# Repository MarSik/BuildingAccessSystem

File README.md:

# NFC entry system using TI Tiva C platform - with DESfire support

The aim is to use the [Tiva C Launchpad](http://www.ti.com/tool/ek-tm4c123gxl) together with [PN532 NFC interface boards](https://www.adafruit.com/products/364) to create a secure building access system.

This project is based on [Elmu's code for Teensy](http://www.codeproject.com/Articles/1096861/DIY-electronic-RFID-Door-Lock-with-Battery-Backup).

## Development environment

Please download [Energia](http://energia.nu), use the `Tools / Board / Board manager` menu item to download the Tiva/Stellaris support files and open the `DoorOpenerSketch.ino` file in it.

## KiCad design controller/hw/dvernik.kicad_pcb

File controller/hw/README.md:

# Controller board

The PCB is not the best routed board ever, but I wanted a single copper layer board for a home made prototype to verify the functionality.

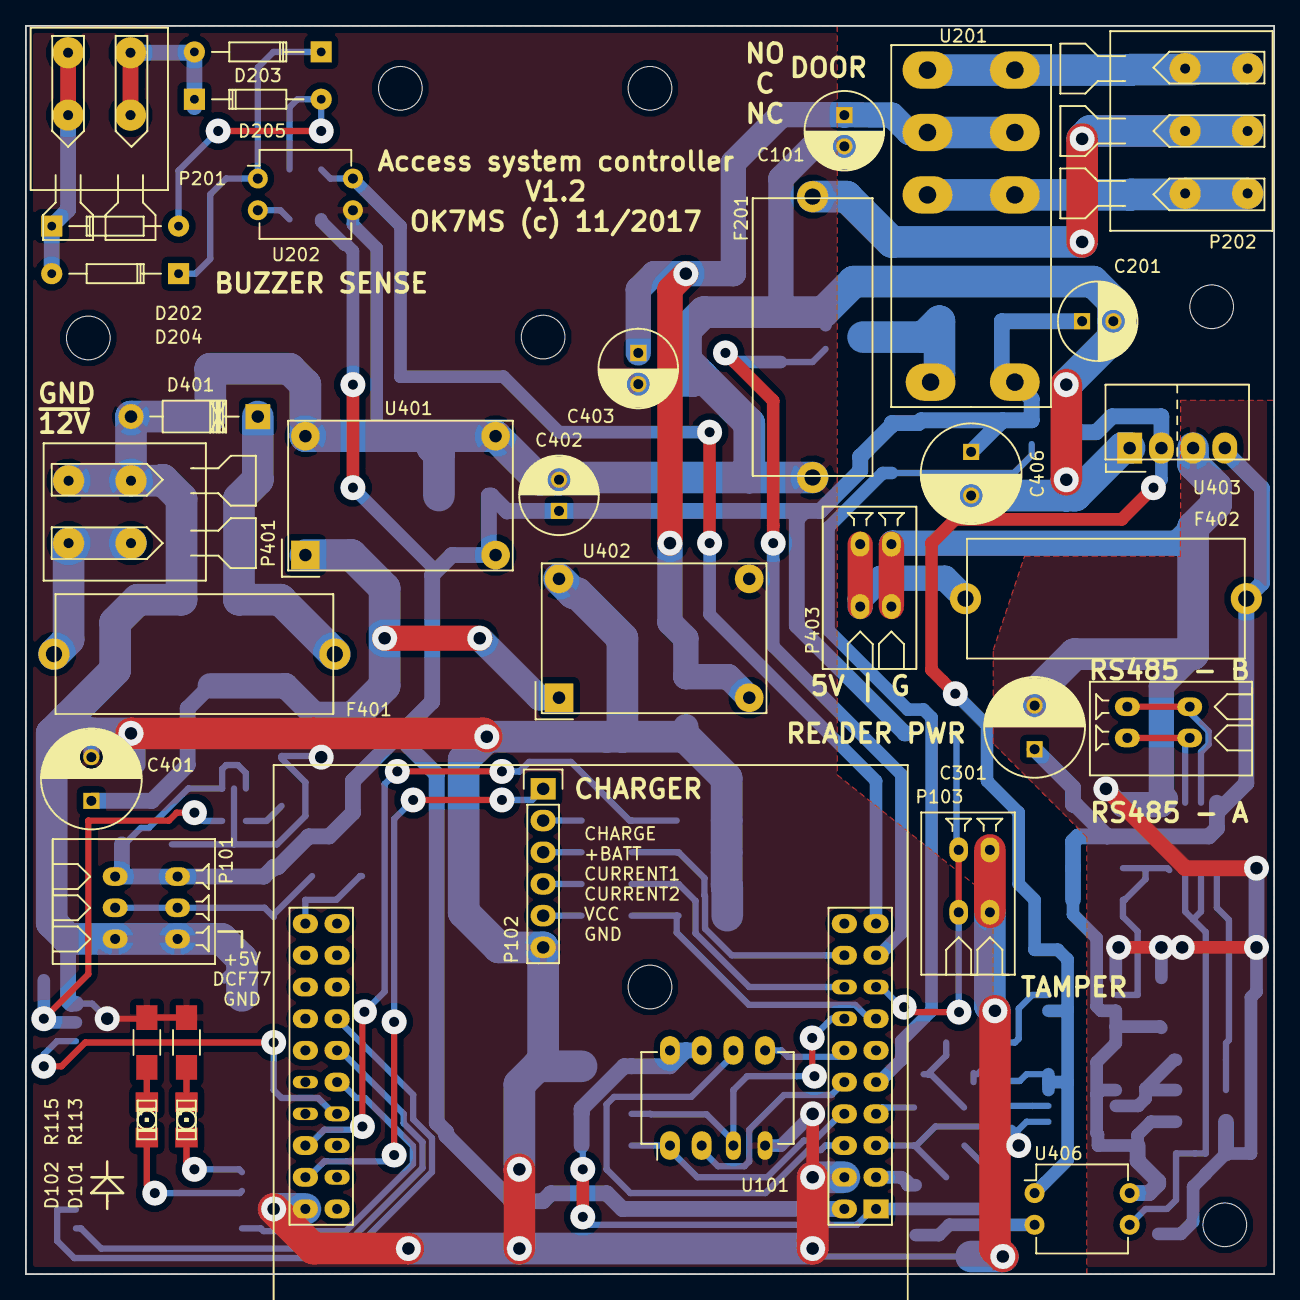
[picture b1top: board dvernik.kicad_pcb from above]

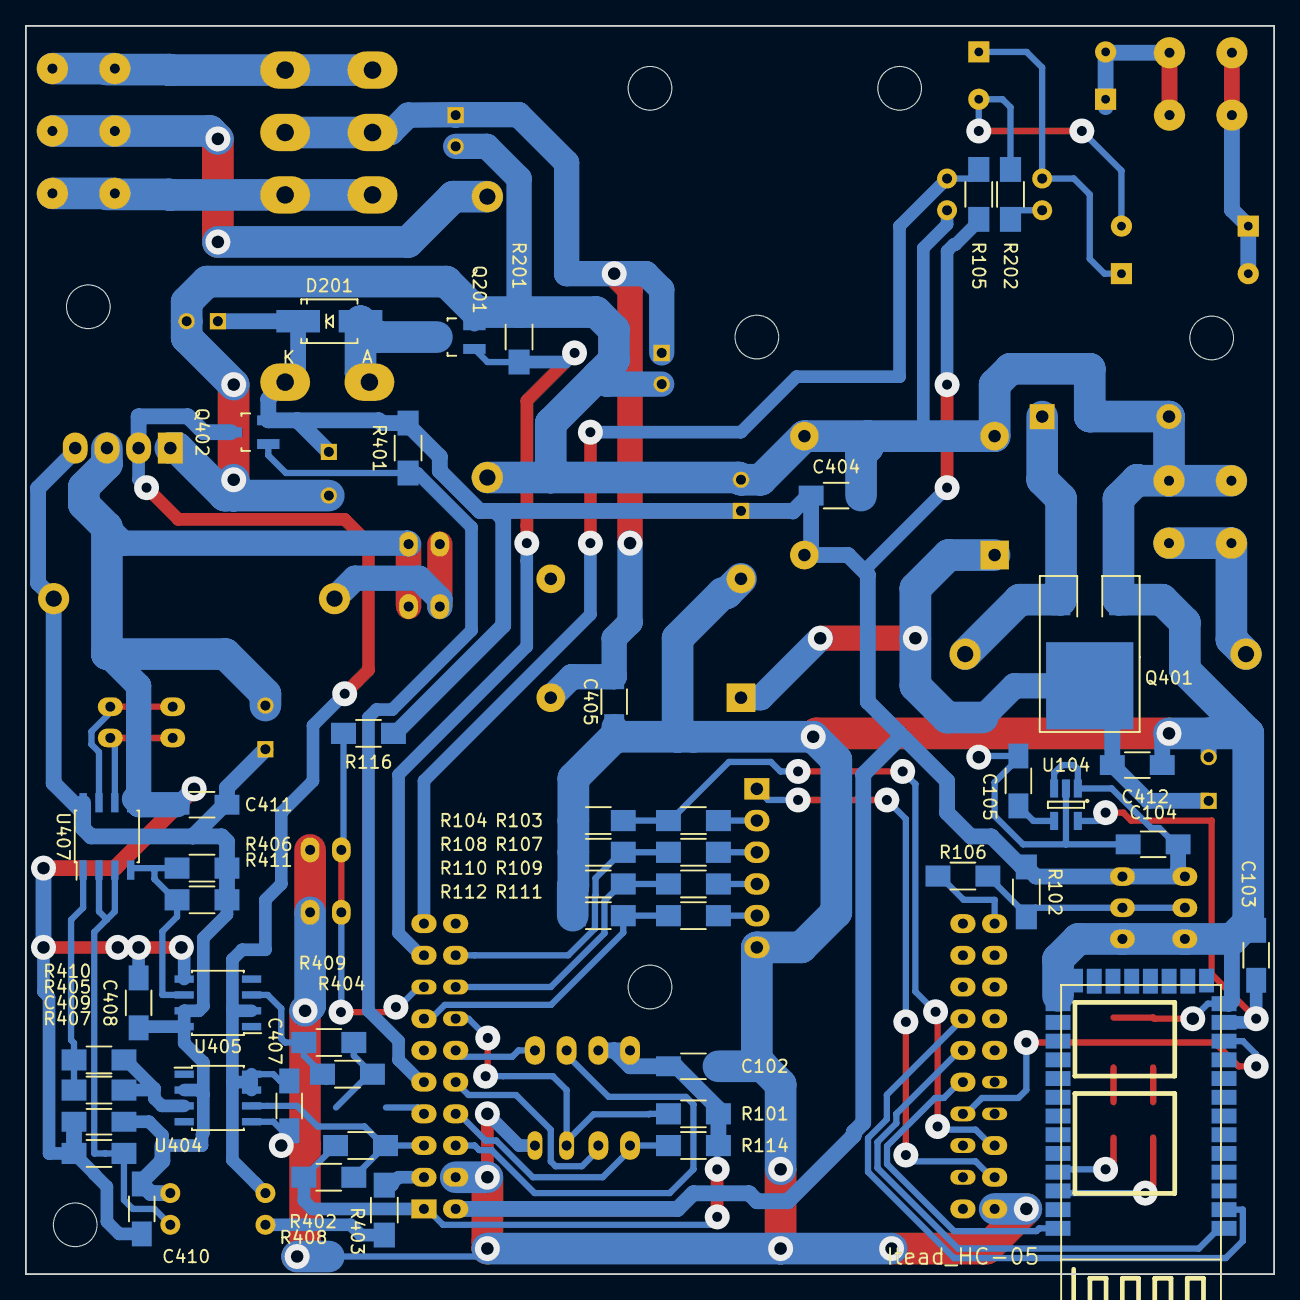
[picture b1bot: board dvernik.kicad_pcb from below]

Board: 2 copper layers, 100.0 x 100.0 mm, 83 parts (48 on the bottom side), 61 nets.

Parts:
C101, C201, C402, C403: Jamicon_220uF_16V_TKP; C_Radial_D6.3_L11.2_P2.5
C102, C104, C105, C404, C405, C412: C; C_1206_HandSoldering
C103, C407, C408, C409, C410, C411: 100n; C_1206_HandSoldering
C301, C401, C406: Jamicon_220uF_25V; C_Radial_D8_L11.5_P3.5
D101, D102: LED; LED-1206
D201: SK110; Diode-SMA_Handsoldering
D202, D203, D204, D205: SD103A; Diode_DO-35_SOD27_Horizontal_RM10
D401: BZX85C15; Diode_DO-41_SOD81_Horizontal_RM10
F201, F401, F402: FUSE; Fuse_5x20_Schurter-0031-8201
P101: WAGO233; Wire-3_Wago-233-P2.5mm
P102: CONN_01X06; Pin_Header_Straight_1x06
P103: CONN_01X02; Wire-2_Wago-233-P2.5mm
P201, P401: WAGO255; Wire-2_WAGO-255_P5mm_HandSoldering
P202: WAGO255; Wire-3_WAGO-255_P5mm_HandSoldering
P402, P403: Wago_233-502; Wire-2_Wago-233-P2.5mm
Q201: 2N7002K; SOT-23_HandSoldering
Q401: IRFU9024; DPAK_HandSoldering
Q402: IRLML6402; SOT-23_HandSoldering
R101, R102, R105, R114, R401, R407: 10k; R_1206_HandSoldering
R103, R107, R109, R111: 100k; R_1206_HandSoldering
R104, R108, R110, R112: 25k; R_1206_HandSoldering
R106: 0; R_1206_HandSoldering
R113, R115, R116, R201, R202, R403: R; R_1206_HandSoldering
R402, R404, R405, R406, R408, R409, R410, R411: 1k; R_1206_HandSoldering
U101: A25L40P; DIP-8_W300mil_LongPads
U102: EK-TM4C123GXL; TI-Launchpad_4-Ports_LargePads
U103: Itead_HC-05; RF_HC-0X_Itead_HandSoldering
U104: LP2992AIM5-3.3CT-ND; SOT-23-5_HandSoldering
U201: JQX-14FC22CS8-5.0; Relay_JQX-14FC_L5_HandSoldering
U202, U406: Cosmo_1010-817; DIP-4_W300mil
U401, U402: Mini-360; DcDc_MH_MINI_360
U403: ROE-0505S; DcDc_Roe_SIP-4
U404, U405: HCPL-0601-500E; SOIC-8_3.9x4.9mm_Pitch1.27mm
U407: SN75176BDR; SOIC-8_3.9x4.9mm_Pitch1.27mm

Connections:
+3V3: C102.1, R101.1, R114.1, R402.2, R408.2, U101.7, U101.8, U102.1.01
+5V: C104.1, C201.1, C402.1, C404.1, C406.1, D201.1, P101.1, Q402.2, R102.1, R105.1, R116.1, R401.2, U102.3.01, U104.1, U104.3, U201.8, U401.2
+5VA: C301.1, C408.1, C409.2, C410.2, C411.2, F402.2, R406.1, R411.1, U403.4, U404.2, U405.7, U405.8, U406.4, U407.8
+12V: C101.1, C403.1, C405.1, U201.3, U201.6, U402.2
+BATT: P102.2, R103.1
/BATT_SENSE: R103.2, R104.1, U102.2.03
/BT_AT_~COMM: U102.4.05, U103.34
/BUZZ1: R105.2, U102.1.10, U202.4
/CHARGE: P102.1, U102.2.02
/CHARGE_SENSE1: P102.4, R109.1
/CHARGE_SENSE2: P102.3, R107.1
/CPU_RX: R402.1, R408.1, U102.1.03, U404.6
/CPU_RX_BT: U102.4.06, U103.1
/CPU_TX_BT: U102.4.07, U103.2
/DCF77: R106.2, U102.2.10
/DOOR1: Q201.1, R201.1, U102.1.09
/Door1/BUZZER_COM: F201.1, P202.2
/Door1/BUZZER_IN1: D203.2, D205.1, P201.1
/Door1/BUZZER_IN2: D202.1, D204.2, P201.2
/Door1/BUZZER_NC: P202.1, U201.2, U201.7
/Door1/BUZZER_NO: P202.3, U201.4, U201.5
/Door1/RELAYGND: D201.2, Q201.3, U201.1
/MEM_CS: R114.2, U101.1, U102.3.04
/MEM_MISO: U101.2, U102.3.05
/MEM_MOSI: U101.5, U102.3.06
/MEM_SCK: U101.6, U102.3.03
/MEM_WP: R101.2, U101.3, U102.3.07
/Power/PFUSED: D401.1, F401.1, Q401.3
/Power/PIN: F401.2, P401.2
/ReaderIntf/485A: P402.1, U407.6
/ReaderIntf/485B: P402.2, U407.7
/ReaderIntf/CPU_TX5: R404.2, R409.2
/ReaderIntf/DCDCIN5V: C407.2, Q402.3, U403.2, U404.7, U404.8, U405.2, U406.1
/ReaderIntf/UNSAFE_RX: R405.1, R410.1, U407.1
/ReaderIntf/UNSAFE_TX: R406.2, R411.2, U405.6, U407.4
/ReaderIntf/~READER_ON: Q402.1, R401.1
/TAMPER: P103.1, R116.2, U102.1.08
/~BT_RESET: U102.4.04, U103.11
/~TX_EN: R403.2, U102.1.02
GND: C101.2, C102.2, C103.2, C104.2, C105.2, C201.2, C401.2, C402.2, C403.2, C404.2, C405.2, C406.2, C407.1, C412.2, D401.2, F201.2, P101.3, P102.6, P103.2, P401.1, Q201.2, Q401.1, R104.2, R108.2, R110.2, R112.2, R113.1, R115.1, R201.2, U101.4, U102.2.01, U102.3.02, U103.13, U103.21, U103.22, U104.2, U202.3, U401.3, U401.4, U402.3, U402.4, U403.1, U404.5
GNDA: C301.2, C408.2, C409.1, C410.1, C411.1, P403.2, R407.2, U403.3, U405.5, U407.5
unnamed: C103.1, U103.12, U104.5
unnamed: C105.1, U104.4
unnamed: C401.1, C412.1, Q401.4, U401.1, U402.1
unnamed: D101.1, R113.2
unnamed: D101.2, U103.31
unnamed: D102.1, R115.2
unnamed: D102.2, U103.32
unnamed: D202.2, D205.2, R202.2
unnamed: D203.1, D204.1, U202.1
unnamed: F402.1, P403.1
unnamed: P101.2, R102.2, R106.1
unnamed: R107.2, R108.1, U102.3.09
unnamed: R109.2, R110.1, U102.3.08
unnamed: R111.2, R112.1, U102.1.07
unnamed: R202.1, U202.2
unnamed: R403.1, U406.2
unnamed: R404.1, R409.1, U405.3
unnamed: R405.2, R410.2, U404.3
unnamed: R407.1, U406.3, U407.2, U407.3
VCC: P102.5, R111.1

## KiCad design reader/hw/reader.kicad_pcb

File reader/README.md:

# remote RFID card reader with RS485 interface

## Building

- Install embedded cmake tooling (github.com/MarSik/embc)
- run `embc init mke04` to initialize the build environment
- run `embc build` to build

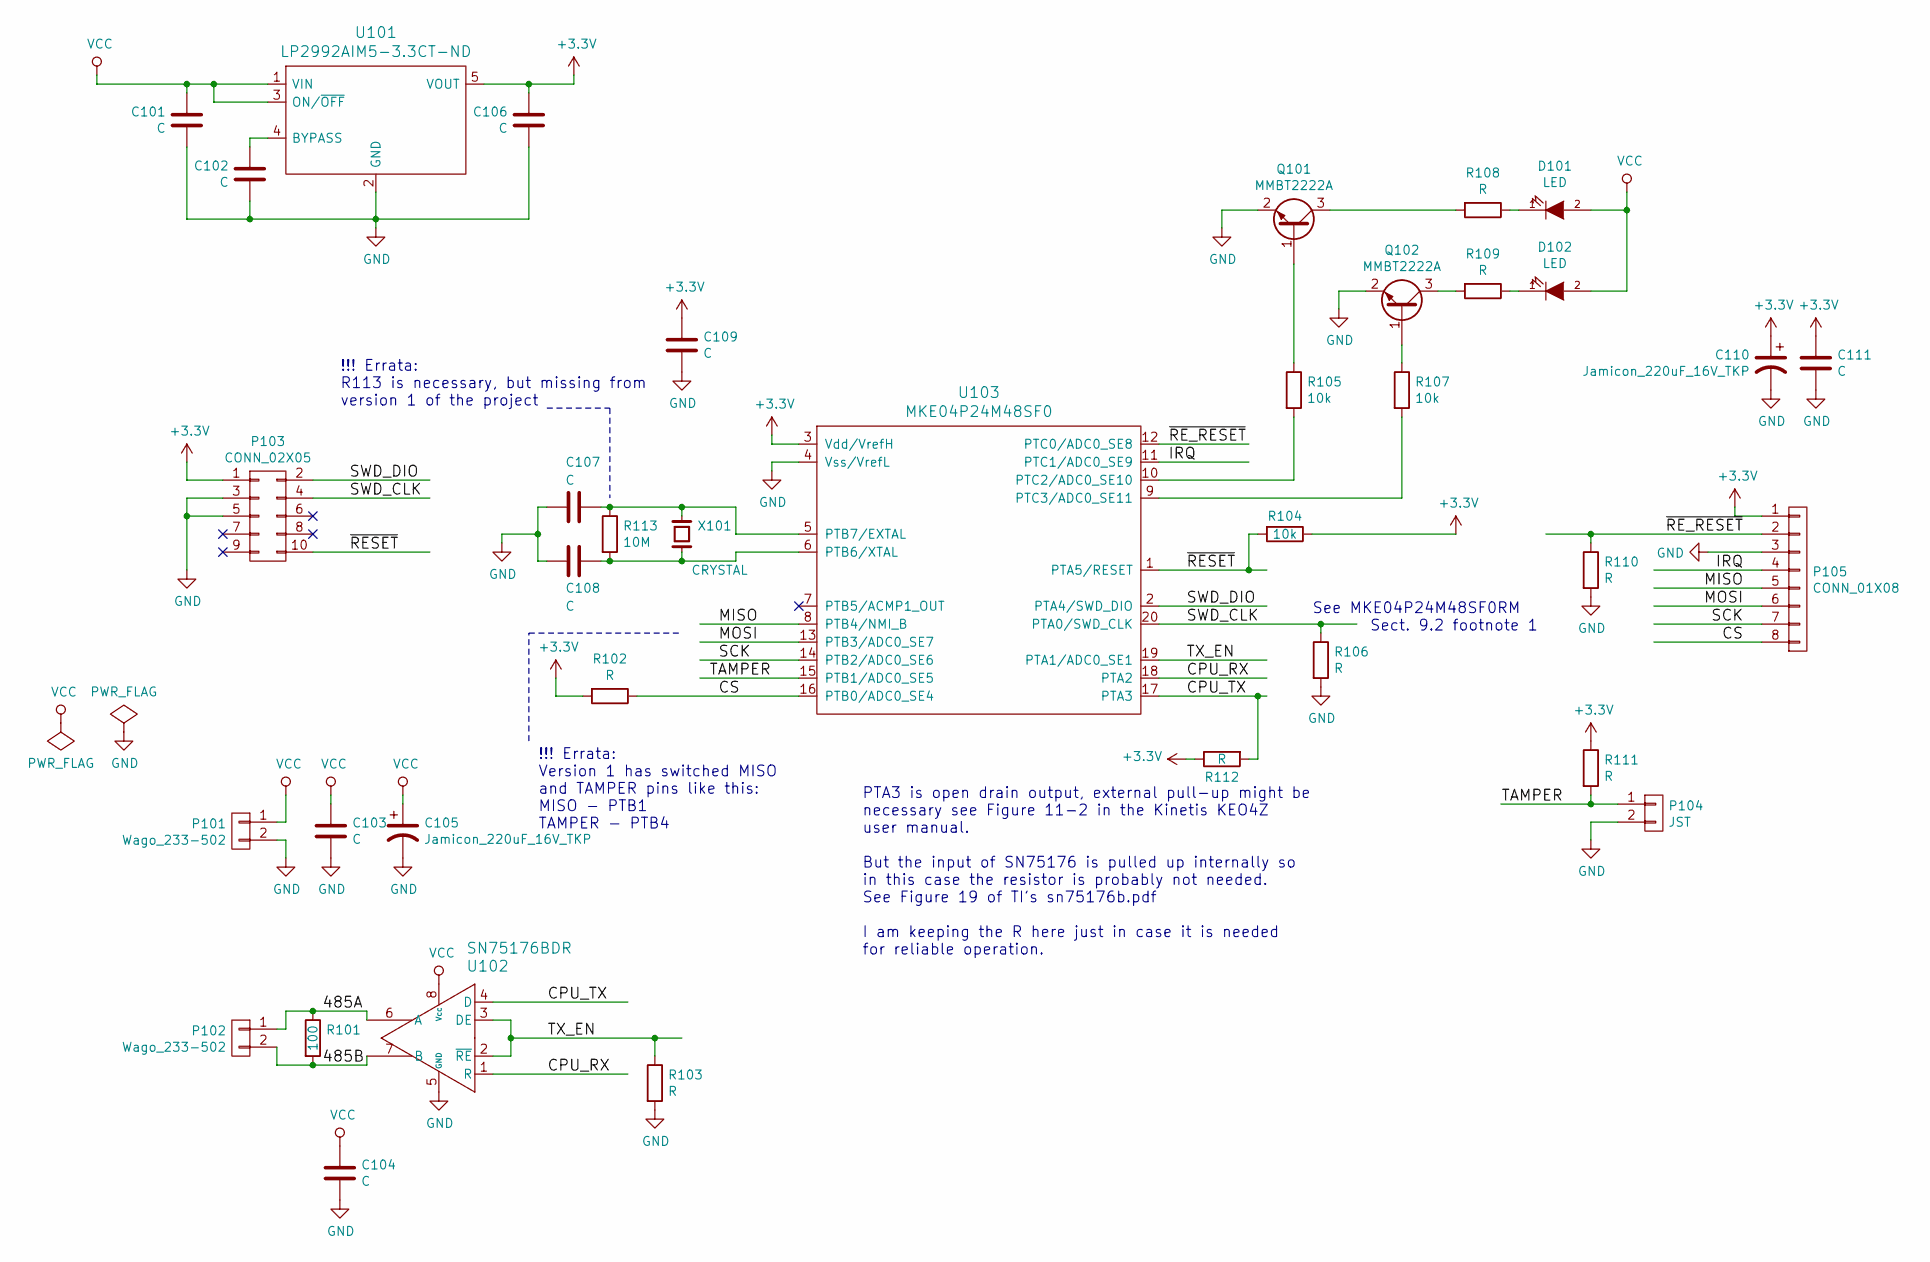
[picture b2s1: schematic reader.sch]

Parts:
C101, C102, C103, C104, C106, C107, C108, C109, C111: C; C_1206_HandSoldering
C105, C110: Jamicon_220uF_16V_TKP; C_Radial_D6.3_L11.2_P2.5
D101, D102: LED; LED-1206
P101, P102: Wago_233-502; Wire-2_Wago-233-P2.5mm
P103: CONN_02X05; Pin_Header_Straight_2x05
P104: JST; Connector_JST_PHR-2
P105: CONN_01X08; Pin_Header_Straight_1x08
Q101, Q102: MMBT2222A; SOT-23_HandSoldering
R101: 100; R_1206_HandSoldering
R102, R103, R106, R108, R109, R110, R111, R112: R; R_1206_HandSoldering
R104, R105, R107: 10k; R_1206_HandSoldering
R113: 10M; R_1206_HandSoldering
U101: LP2992AIM5-3.3CT-ND; SOT-23-5_HandSoldering
U102: SN75176BDR; SOIC-8_3.9x4.9mm_Pitch1.27mm
U103: MKE04P24M48SF0; SOIC-20_7.5x12.8mm_Pitch1.27mm
X101: CRYSTAL; Crystal_HC49-U_Vertical

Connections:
+3V3: C106.1, C109.1, C110.1, C111.1, P103.1, P105.1, R102.2, R104.1, R111.1, R112.1, U101.5 (VOUT), U103.3 (Vdd/VrefH)
/485A: P102.1, R101.1, U102.6 (A)
/485B: P102.2, R101.2, U102.7 (B)
/CPU_RX: U102.1 (R), U103.18 (PTA2)
/CPU_TX: R112.2, U102.4 (D), U103.17 (PTA3)
/CS: P105.8, R102.1, U103.16 (PTB0/ADC0_SE4)
/IRQ: P105.4, U103.11 (PTC1/ADC0_SE9)
/MISO: P105.5, U103.8 (PTB4/NMI_B)
/MOSI: P105.6, U103.13 (PTB3/ADC0_SE7)
/SCK: P105.7, U103.14 (PTB2/ADC0_SE6)
/SWD_CLK: P103.4, R106.1, U103.20 (PTA0/SWD_CLK)
/SWD_DIO: P103.2, U103.2 (PTA4/SWD_DIO)
/TAMPER: P104.1, R111.2, U103.15 (PTB1/ADC0_SE5)
/TX_EN: R103.1, U102.2 (~RE), U102.3 (DE), U103.19 (PTA1/ADC0_SE1)
/~RESET: P103.10, R104.2, U103.1 (PTA5/RESET)
/~RE_RESET: P105.2, R110.1, U103.12 (PTC0/ADC0_SE8)
GND: C101.2, C102.2, C103.2, C104.2, C105.2, C106.2, C107.2, C108.2, C109.2, C110.2, C111.2, P101.2, P103.3, P103.5, P104.2, P105.3, Q101.2 (E), Q102.2 (E), R103.2, R106.2, R110.2, U101.2 (GND), U102.5 (GND), U103.4 (Vss/VrefL)
unnamed: C102.1, U101.4 (BYPASS)
unnamed: C107.1, R113.1, U103.5 (PTB7/EXTAL), X101.1
unnamed: C108.1, R113.2, U103.6 (PTB6/XTAL), X101.2
unnamed: D101.1 (K), R108.1
unnamed: D102.1 (K), R109.1
unnamed: Q101.1 (B), R105.1
unnamed: Q101.3 (C), R108.2
unnamed: Q102.1 (B), R107.1
unnamed: Q102.3 (C), R109.2
unnamed: R105.2, U103.10 (PTC2/ADC0_SE10)
unnamed: R107.2, U103.9 (PTC3/ADC0_SE11)
VCC: C101.1, C103.1, C104.1, C105.1, D101.2 (A), D102.2 (A), P101.1, U101.1 (VIN), U101.3 (ON/~OFF), U102.8 (Vcc)

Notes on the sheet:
See MKE04P24M48SF0RM Sect. 9.2 footnote 1
PTA3 is open drain output, external pull-up might be necessary see Figure 11-2 in the Kinetis KEO4Z user manual. But the input of SN75176 is pulled up internally so in this case the resistor is probably not needed. See Figure 19 of TI's sn75176b.pdf I am keeping the R here just in case it is needed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
!!! Errata: Version 1 has switched MISO and TAMPER pins like this: MISO - PTB1 TAMPER - PTB4
!!! Errata: R113 is necessary, but missing from version 1 of the project

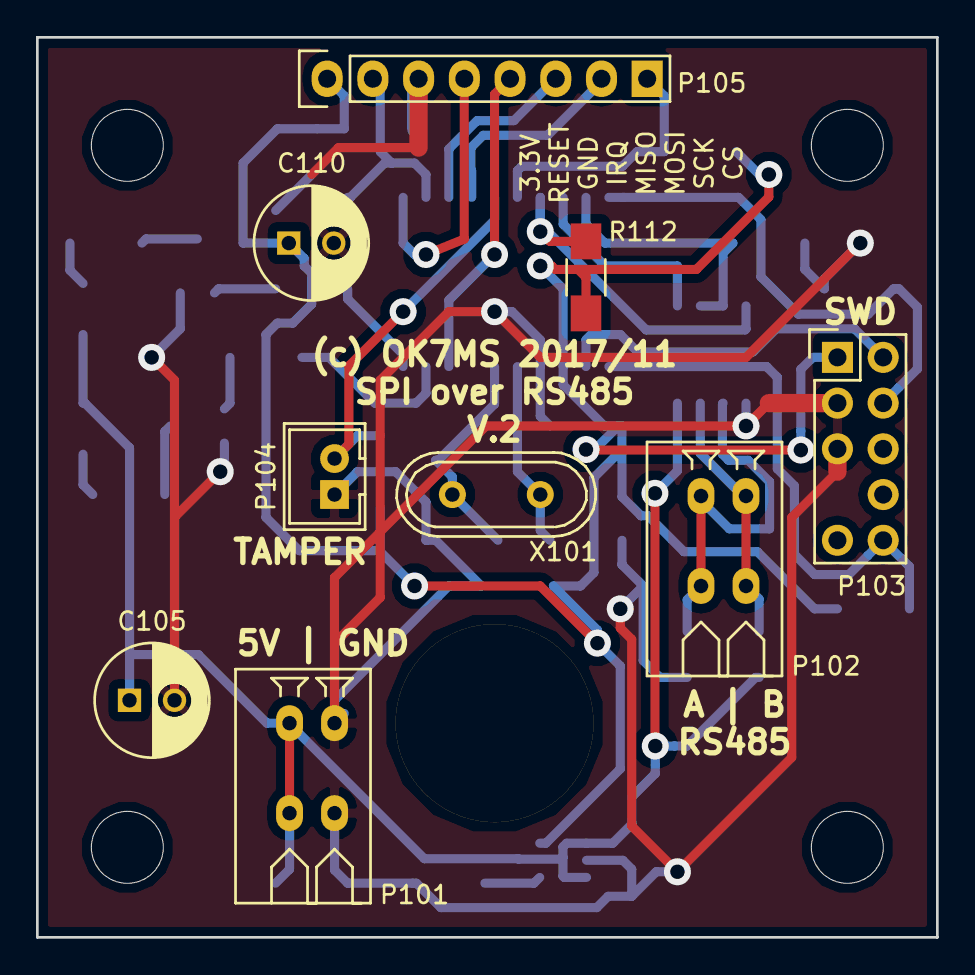
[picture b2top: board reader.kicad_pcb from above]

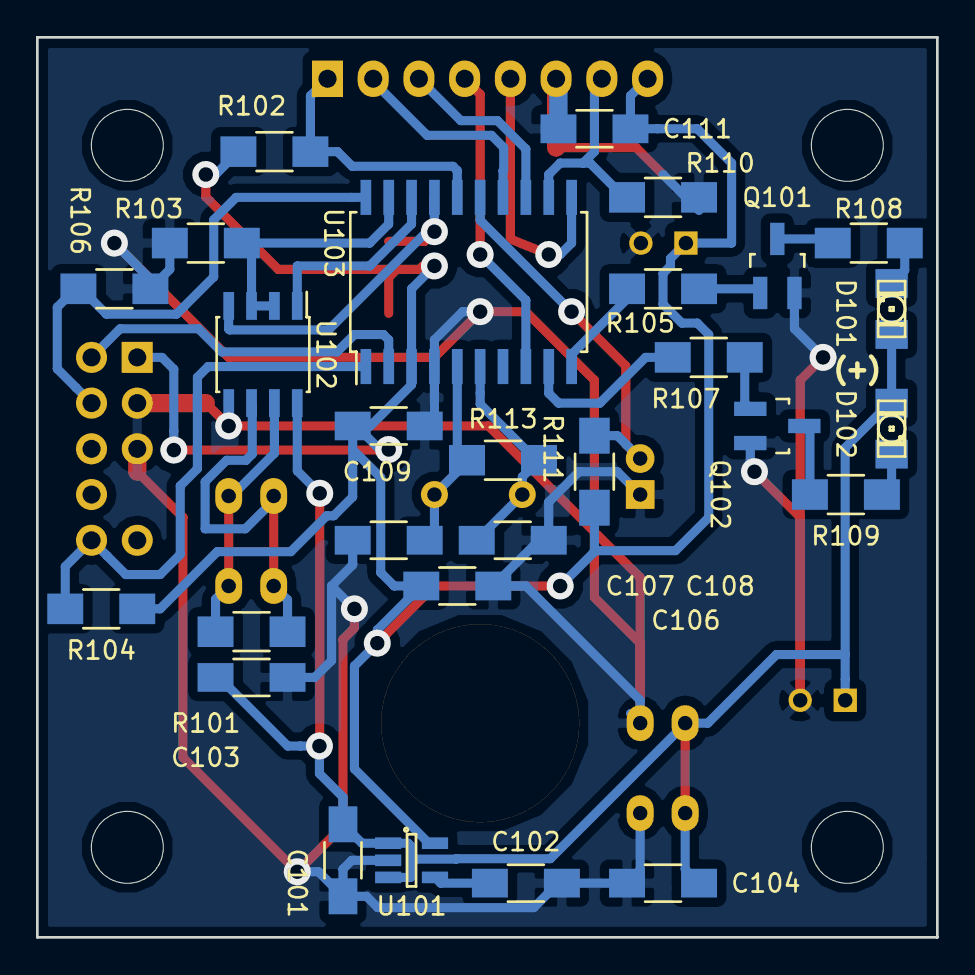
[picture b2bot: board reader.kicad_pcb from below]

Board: 2 copper layers, 50.0 x 50.0 mm, 37 parts (28 on the bottom side), 29 nets.

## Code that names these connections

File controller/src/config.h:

#ifndef PROJECT_CONFIG_H
#define PROJECT_CONFIG_H

// This password will be required when entering via Terminal
// If you define an empty string here, no password is requested.
// If any unauthorized person may access the dooropener hardware phyically you should provide a password!
#define PASSWORD  ""
// The interval of inactivity in minutes after which the password must be entered again (automatic log-off)
#define PASSWORD_TIMEOUT  5

// The tick counter starts at zero when the CPU is reset.
// This interval is added to the 64 bit tick count to get a value that does not start at zero,
// because gu64_LastPasswd is initialized with 0 and must always be in the past.
#define PASSWORD_OFFSET_MS   (2 * PASSWORD_TIMEOUT * 60 * 1000)

// This Arduino / Teensy pin is connected to the relay that opens the door 1
#define DOOR_PIN       PA_6
// Sensing whether someone is pushing the door open button
#define BUZZ_SENSE     PA_7

// Tamper detection pin
#define TAMPER         PA_5

// This Arduino / Teensy pin is connected to the transistor that charges the battery
#define CHARGE_PIN       PB_2
#define CHARGE_BATTERY_ADC A3
#define CHARGE_CURR1_ADC A1
#define CHARGE_CURR2_ADC A0
#define CHARGE_VCC_ADC A10

// Bluetooth pins
#define BT_RESET PC_4
#define BT_AT PC_5 // AT log.1, communication log.0
#define BT_SERIAL 3

// SPI flash memory
#define MEM_CS PD_1
#define MEM_SPI 3
#define MEM_WP PE_1 // WP log.0

// Reader
// Make sure the TX pin can provide at least 8mA
#define READER_SERIAL 1
#define READER_TX PB_5 // TX active log.0
#define READER_ON PE_4 // ON log.0

// This Arduino / Teensy pin is connected to the reader RSTPDN pin (reset the reader)
// When a communication error with the reader is detected the board is reset automatically.
#define RESET_PIN         READER_ON


// This Arduino / Teensy pin is connected to the green LED in a two color LED.
// The green LED flashes fast while no card is present and flashes 1 second when opening the door.
#define LED_GREEN_PIN    GREEN_LED

// This Arduino / Teensy pin is connected to the red LED in a two color LED.
// The red LED flashes slowly when a communication error occurred with the reader chip and when an unauthorized person tries to open the door.
// It flashes fast when a power failure has been detected. (Charging battery failed)
#define LED_RED_PIN      RED_LED

// This Arduino / Teensy pin is connected to the voltage divider that measures the 13,6V battery voltage
#define VOLTAGE_MEASURE_PIN  CHARGE_BATTERY_ADC

// Use 12 bit resolution for the analog input (ADC)
// The Teensy 3.x boards have a 12 bit ADC.
#define ANALOG_RESOLUTION  12

// The analog reference voltage (float) of the CPU (analogReference(DEFAULT) --> 3.3V, analogReference(INTERNAL1V2) --> 1.2V)
#define ANALOG_REFERENCE   1.2

// This factor (float) is used to calculate the battery voltage.
// If the external voltage divider is 220 kOhm / 15 kOhm the factor is theoretically 15.66666 == (220 + 15) / 15.
// You must fine tune this value until the battery voltage is displayed correctly when you hit Enter in the Terminal.
// Therefor you must unplug the 220V power suppply and measure the real voltage at the battery.
#define VOLTAGE_FACTOR   15.9

// The interval in milliseconds that the relay is powered which opens the door
#define OPEN_INTERVAL   1000

// This is the interval that the RF field is switched off to save battery.
// The shorter this interval, the more power is consumed by the reader.
// The longer  this interval, the longer the user has to wait until the door opens.
// The recommended interval is 1000 ms.
#define RF_OFF_INTERVAL  500

#ifndef LED_BUILTIN
#define LED_BUILTIN BLUE_LED
#endif // LED_BUILTIN

// DCF77 receiver
#define DCF77_PIN PA_2

#endif

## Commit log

2017-03-21 Initial import of partially ported code
2017-03-21 Add README
2017-04-04 [WIP] Use hight speed uart instead of spi
2017-04-08 Wakeup is needed for every command, fix Serial1 defs and timeouts
2017-04-16 Small cleanup of constants
2017-04-19 Use platformio
2017-04-19 Tweak platformio build options
2017-04-19 Add an empty dir for HC05 library
2017-04-19 WIP Ultralight C support
2017-04-21 WIP RC522 support
2017-04-23 Add (modified) RC522 library
2017-04-23 More source hacks to compile for RC522 (SPI and does not work yetpio run)
2017-04-28 WIP Ultralight C auth
2017-04-29 Ultralight authentication is working
2017-04-29 Playing around with card id format
2017-04-29 Fix cardId to uint32_t conversion and detection of no card in the field
2017-04-29 Basic card personalization and app detection
2017-04-30 Add CRC to door rule block that is stored to card
2017-04-30 Add some Ultralight C page constants
2017-04-30 Use page constants when changing key for Ultralight and add the secure pages call
2017-05-03 More syntax fixes to compile with separated Mifare files
2017-05-03 Remove pointer aliasing warning
2017-05-03 Rename .ino files to .cpp
2017-05-03 Add the starting torso of CardManager class
2017-05-04 WIP centralize and abstract card management routines
2017-05-05 Fix compilation with card manager
2017-05-05 Remove user manager
2017-05-06 Code and string cleanup
2017-05-08 WIP Use UART mode with better error handling
2017-05-08 Fixed UART mode - it now reads Ultraliht C properly
    But the first RC522 init sequence still fails and triggers
    RC522 restart. All seems to work after that.
    Error handling of post-select communication needs to be
    improved too.
2017-05-08 Add logging abstraction to avoid direct usage of Serial from libraries
2017-05-14 v1 of controller PCB, mostly single layer with a few jumpers
2017-05-15 Fix drill sizes, silkscreen and add name and version markings
2017-05-20 Add reader board
2017-05-22 Slight improvements to hardware design
2017-05-25 Restructure files and small updates
2017-06-03 Add some timeouts to MFRC code and DCF support to the main code
2017-06-07 Fix silkscreen
2017-06-10 Fix voltage for SPI flash, short under one capacitor
2017-06-10 Save latest changes to sch
2017-06-15 Fix door pin definition
2017-06-15 Pin definitions according to the built board
2017-07-30 Describe embc based build
2017-11-05 Use Freescale header for MKE04
2017-11-12 Playing with reader soource code
2017-11-14 Play with LEDs
2017-11-18 New KiCAD lib references, crystal feedback R, basic uart impl
2017-11-20 SPI bridge implementation
2017-11-21 Fix MISO/TAMPER issue, fix watchdog, fix corruption when SPI cmd + 1 byte data
2017-11-23 Align reader & controller to use SPI over RS485
2017-11-23 Some small improvements to controller - reader interaction
2017-11-26 Compilability using embc lm4f, fixes to TX_EN switching
2017-11-27 Fix serious hw bug (5V level on 3.3V tolerant RX/TX on ctrl board)
2017-11-28 Use git submodules and do not ignore CMakelists.cmake
2017-11-28 Fix controller issues with 3.3V CPU interfacing 5V logic
2017-11-28 Add missing CMakeLists.txt files
2017-11-28 Ignore IDEA (CLion) metadata files
2017-11-30 Make controller compilable on clean system and with latest libs
2017-12-02 Configure ETL
2017-12-02 Use Arduino library prepared by FindArduino
2017-12-02 WIP Still working in 3.3 - 5V interface issues
2017-12-02 Configure open drain ouputs and use TX_EN properly
2017-12-04 Disable NMI in reader board
2017-12-04 Update WDT init sequence
2017-12-05 WDT timer counter is big-endian!
2017-12-05 WIP updates to controller - open drain, style, debugging, pin defs
2017-12-08 Fixes controller writeBye escaping and allows remote SPI configuration
2017-12-09 Improvements to configurability and efficiency
2017-12-10 Fix response delay timing (5ms -> 125us) and other time constants a bit
2017-12-13 WIP fill in missing bits to card manager and personalization procedures
2017-12-13 Fix CRC deserialization when reading card data
2017-12-13 Flash red led when card is rejected
2017-12-14 WIP state machine
2017-12-14 Separate pin assignments to config.h
2017-12-16 Rewrite the controller logic to state machine
2017-12-21 Implement master key changes
2017-12-22 Use separate key for each card!
2018-01-02 WIP bluetooth support - cpu freezes after btinit
2018-01-02 schematic improvements (door state pin for controller, fixes)
2018-01-05 Enable stack protector for controller
2018-01-06 Add missing stack protector symbols
2018-01-07 Fix BT serial bug (sleev vs. delay), use etl::string for command buffer and reenable DCF
2018-01-07 Small #define fix
2024-10-19 Const optimizations
2024-10-19 Missing files?
